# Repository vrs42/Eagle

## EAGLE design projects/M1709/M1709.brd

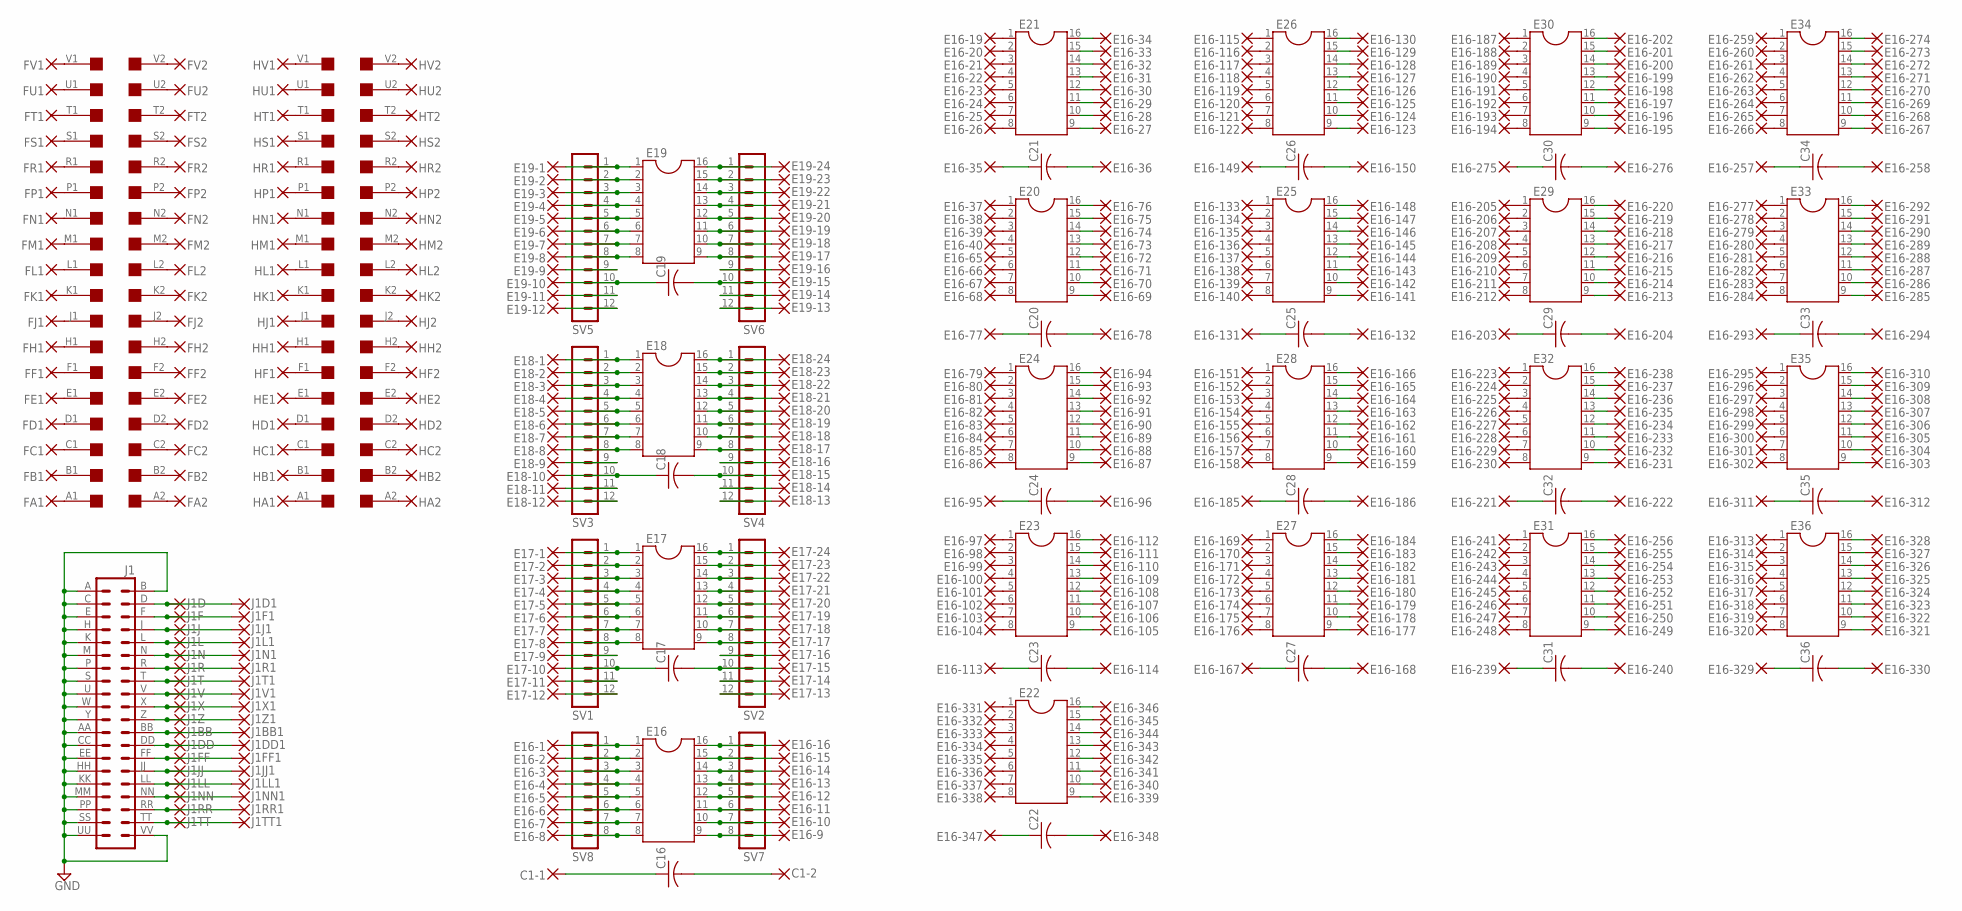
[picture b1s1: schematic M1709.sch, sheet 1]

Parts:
C1-1, C1-2: 1,6/0,8
C16, C17, C18, C19, C20, C21, C22, C23, C24, C25, C26, C27, C28, C29, C30, C31, C32, C33, C34, C35, C36: C-US075-032X103; C075-032X103
E16, E17, E18, E19, E20, E21, E22, E23, E24, E25, E26, E27, E28, E29, E30, E31, E32, E33, E34, E35, E36: DIL16
E16-1, E16-2, E16-3, E16-4, E16-5, E16-6, E16-7, E16-8, E16-9, E16-10, E16-11, E16-12, E16-13, E16-14, E16-15, E16-16, E17-1, E17-2, E17-3, E17-4, E17-5, E17-6, E17-7, E17-8, E17-9, E17-10, E17-11, E17-12, E17-13, E17-14, E17-15, E17-16, E17-17, E17-18, E17-19, E17-20, E17-21, E17-22, E17-23, E17-24, E18-1, E18-2, E18-3, E18-4, E18-5, E18-6, E18-7, E18-8, E18-9, E18-10, E18-11, E18-12, E18-13, E18-14, E18-15, E18-16, E18-17, E18-18, E18-19, E18-20, E18-21, E18-22, E18-23, E18-24, E19-1, E19-2, E19-3, E19-4, E19-5, E19-6, E19-7, E19-8, E19-9, E19-10, E19-11, E19-12, E19-13, E19-14, E19-15, E19-16, E19-17, E19-18, E19-19, E19-20, E19-21, E19-22, E19-23, E19-24: 1,6/0,8
E16-19, E16-20, E16-21, E16-22, E16-23, E16-24, E16-25, E16-26, E16-27, E16-28, E16-29, E16-30, E16-31, E16-32, E16-33, E16-34, E16-35, E16-36, E16-37, E16-38, E16-39, E16-40, E16-65, E16-66, E16-67, E16-68, E16-69, E16-70, E16-71, E16-72, E16-73, E16-74, E16-75, E16-76, E16-77, E16-78, E16-79, E16-80, E16-81, E16-82, E16-83, E16-84, E16-85, E16-86, E16-87, E16-88, E16-89, E16-90, E16-91, E16-92, E16-93, E16-94, E16-95, E16-96, E16-97, E16-98, E16-99, E16-100, E16-101, E16-102, E16-103, E16-104, E16-105, E16-106, E16-107, E16-108, E16-109, E16-110, E16-111, E16-112, E16-113, E16-114, E16-115, E16-116, E16-117, E16-118, E16-119, E16-120, E16-121, E16-122, E16-123, E16-124, E16-125, E16-126, E16-127, E16-128, E16-129, E16-130, E16-131, E16-132, E16-133, E16-134, E16-135, E16-136, E16-137, E16-138, E16-139, E16-140, E16-141, E16-142, E16-143, E16-144, E16-145, E16-146, E16-147, E16-148, E16-149, E16-150, E16-151, E16-152, E16-153, E16-154, E16-155, E16-156, E16-157, E16-158, E16-159, E16-160, E16-161, E16-162, E16-163, E16-164, E16-165, E16-166, E16-167, E16-168, E16-169, E16-170, E16-171, E16-172, E16-173, E16-174, E16-175, E16-176, E16-177, E16-178, E16-179, E16-180, E16-181, E16-182, E16-183, E16-184, E16-185, E16-186, E16-187, E16-188, E16-189, E16-190, E16-191, E16-192, E16-193, E16-194, E16-195, E16-196, E16-197, E16-198, E16-199, E16-200, E16-201, E16-202, E16-203, E16-204, E16-205, E16-206, E16-207, E16-208, E16-209, E16-210, E16-211, E16-212, E16-213, E16-214, E16-215, E16-216, E16-217, E16-218, E16-219, E16-220, E16-221, E16-222, E16-223, E16-224, E16-225, E16-226, E16-227, E16-228, E16-229, E16-230, E16-231, E16-232, E16-233, E16-234, E16-235, E16-236, E16-237, E16-238, E16-239, E16-240, E16-241, E16-242, E16-243, E16-244, E16-245, E16-246, E16-247, E16-248, E16-249, E16-250, E16-251, E16-252, E16-253, E16-254, E16-255, E16-256, E16-257, E16-258, E16-259, E16-260, E16-261, E16-262, E16-263, E16-264, E16-265, E16-266, E16-267, E16-268, E16-269, E16-270, E16-271, E16-272, E16-273, E16-274, E16-275, E16-276, E16-277, E16-278, E16-279, E16-280, E16-281, E16-282, E16-283, E16-284, E16-285, E16-286, E16-287, E16-288, E16-289, E16-290, E16-291, E16-292, E16-293, E16-294, E16-295, E16-296, E16-297, E16-298, E16-299, E16-300, E16-301, E16-302, E16-303, E16-304, E16-305, E16-306, E16-307, E16-308, E16-309, E16-310, E16-311, E16-312, E16-313, E16-314, E16-315, E16-316, E16-317, E16-318, E16-319, E16-320, E16-321, E16-322, E16-323, E16-324, E16-325, E16-326, E16-327, E16-328, E16-329, E16-330, E16-331, E16-332, E16-333, E16-334, E16-335, E16-336, E16-337, E16-338, E16-339, E16-340, E16-341, E16-342, E16-343, E16-344, E16-345, E16-346, E16-347, E16-348: 2,54/0,8
F: SINGLE; EDGE-CON2
FA1, FA2: 2,54/0,8
FB1, FB2: 2,54/0,8
FC1, FC2: 2,54/0,8
FD1, FD2: 2,54/0,8
FE1, FE2: 2,54/0,8
FF1, FF2: 2,54/0,8
FH1, FH2: 2,54/0,8
FJ1, FJ2: 2,54/0,8
FK1, FK2: 2,54/0,8
FL1, FL2: 2,54/0,8
FM1, FM2: 2,54/0,8
FN1, FN2: 2,54/0,8
FP1, FP2: 2,54/0,8
FR1, FR2: 2,54/0,8
FS1, FS2: 2,54/0,8
FT1, FT2: 2,54/0,8
FU1, FU2: 2,54/0,8
FV1, FV2: 2,54/0,8
H: SINGLE; EDGE-CON2
HA1, HA2: 2,54/0,8
HB1, HB2: 2,54/0,8
HC1, HC2: 2,54/0,8
HD1, HD2: 2,54/0,8
HE1, HE2: 2,54/0,8
HF1, HF2: 2,54/0,8
HH1, HH2: 2,54/0,8
HJ1, HJ2: 2,54/0,8
HK1, HK2: 2,54/0,8
HL1, HL2: 2,54/0,8
HM1, HM2: 2,54/0,8
HN1, HN2: 2,54/0,8
HP1, HP2: 2,54/0,8
HR1, HR2: 2,54/0,8
HS1, HS2: 2,54/0,8
HT1, HT2: 2,54/0,8
HU1, HU2: 2,54/0,8
HV1, HV2: 2,54/0,8
J1: DEC40PINH
J1BB, J1BB1, J1D, J1D1, J1DD, J1DD1, J1F, J1F1, J1FF, J1FF1, J1J, J1J1, J1JJ, J1JJ1, J1L, J1L1, J1LL, J1LL1, J1N, J1N1, J1NN, J1NN1, J1R, J1R1, J1RR, J1RR1, J1T, J1T1, J1TT, J1TT1, J1V, J1V1, J1X, J1X1, J1Z, J1Z1: 2,54/0,8
SV1, SV2, SV3, SV4, SV5, SV6: MA12-1
SV7, SV8: MA08-1

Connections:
GND: J1.A (1), J1.AA (23), J1.B (2), J1.C (3), J1.CC (25), J1.E (5), J1.EE (27), J1.H (7), J1.HH (29), J1.K (9), J1.KK (31), J1.M (11), J1.MM (33), J1.P (13), J1.PP (35), J1.S (15), J1.SS (37), J1.U (17), J1.UU (39), J1.VV (40), J1.W (19), J1.Y (21); also elsewhere on the board
unnamed: J1.D (4), J1D.1, J1D1.1
unnamed: J1.F (6), J1F.1, J1F1.1
unnamed: J1.J (8), J1J.1, J1J1.1
unnamed: J1.L (10), J1L.1, J1L1.1
unnamed: J1.N (12), J1N.1, J1N1.1
unnamed: J1.R (14), J1R.1, J1R1.1
unnamed: J1.T (16), J1T.1, J1T1.1
unnamed: J1.V (18), J1V.1, J1V1.1
unnamed: J1.X (20), J1X.1, J1X1.1
unnamed: J1.Z (22), J1Z.1, J1Z1.1
unnamed: J1.BB (24), J1BB.1, J1BB1.1
unnamed: J1.DD (26), J1DD.1, J1DD1.1
unnamed: J1.FF (28), J1FF.1, J1FF1.1
unnamed: J1.JJ (30), J1JJ.1, J1JJ1.1
unnamed: J1.LL (32), J1LL.1, J1LL1.1
unnamed: J1.NN (34), J1NN.1, J1NN1.1
unnamed: J1.RR (36), J1RR.1, J1RR1.1
unnamed: J1.TT (38), J1TT.1, J1TT1.1
unnamed: F.A1, FA1.1
unnamed: F.B1, FB1.1
unnamed: F.C1, FC1.1
unnamed: F.D1, FD1.1
unnamed: F.E1, FE1.1
unnamed: F.F1, FF1.1
unnamed: F.H1, FH1.1
unnamed: F.J1, FJ1.1
unnamed: F.K1, FK1.1
unnamed: F.L1, FL1.1
unnamed: F.M1, FM1.1
unnamed: F.N1, FN1.1
unnamed: F.P1, FP1.1
unnamed: F.R1, FR1.1
unnamed: F.S1, FS1.1
unnamed: F.T1, FT1.1
unnamed: F.U1, FU1.1
unnamed: F.V1, FV1.1
unnamed: F.A2, FA2.1
unnamed: F.B2, FB2.1
unnamed: F.C2, FC2.1
unnamed: F.D2, FD2.1
unnamed: F.E2, FE2.1
unnamed: F.F2, FF2.1
unnamed: F.H2, FH2.1
unnamed: F.J2, FJ2.1
unnamed: F.K2, FK2.1
unnamed: F.L2, FL2.1
unnamed: F.M2, FM2.1
unnamed: F.N2, FN2.1
unnamed: F.P2, FP2.1
unnamed: F.R2, FR2.1
unnamed: F.S2, FS2.1
unnamed: F.T2, FT2.1
unnamed: F.U2, FU2.1
unnamed: F.V2, FV2.1
unnamed: H.A2, HA2.1
unnamed: H.B2, HB2.1
unnamed: H.C2, HC2.1
unnamed: H.D2, HD2.1
unnamed: H.E2, HE2.1
unnamed: H.F2, HF2.1
unnamed: H.H2, HH2.1
unnamed: H.J2, HJ2.1
unnamed: H.K2, HK2.1
unnamed: H.L2, HL2.1
unnamed: H.M2, HM2.1
unnamed: H.N2, HN2.1
unnamed: H.P2, HP2.1
unnamed: H.R2, HR2.1
unnamed: H.S2, HS2.1
unnamed: H.T2, HT2.1
unnamed: H.U2, HU2.1
unnamed: H.V2, HV2.1
unnamed: H.A1, HA1.1
unnamed: H.B1, HB1.1
unnamed: H.C1, HC1.1
unnamed: H.D1, HD1.1
unnamed: H.E1, HE1.1
unnamed: H.F1, HF1.1
unnamed: H.H1, HH1.1
unnamed: H.J1, HJ1.1
unnamed: H.K1, HK1.1
unnamed: H.L1, HL1.1
unnamed: H.M1, HM1.1
unnamed: H.N1, HN1.1
unnamed: H.P1, HP1.1
unnamed: H.R1, HR1.1
unnamed: H.S1, HS1.1
unnamed: H.T1, HT1.1
unnamed: H.U1, HU1.1
unnamed: H.V1, HV1.1
unnamed: E17.1, E17-1.1, SV1.1
unnamed: E17.2, E17-2.1, SV1.2
unnamed: E17.3, E17-3.1, SV1.3
unnamed: E17.4, E17-4.1, SV1.4
unnamed: E17.5, E17-5.1, SV1.5
unnamed: E17.6, E17-6.1, SV1.6
unnamed: E17.7, E17-7.1, SV1.7
unnamed: E17.8, E17-8.1, SV1.8
unnamed: E17-9.1, SV1.9
unnamed: C17.1, E17-10.1, SV1.10
unnamed: C17.2, E17-15.1, SV2.10
unnamed: E17-16.1, SV2.9
unnamed: E17.9, E17-17.1, SV2.8
unnamed: E17.10, E17-18.1, SV2.7
unnamed: E17.11, E17-19.1, SV2.6
unnamed: E17.12, E17-20.1, SV2.5
unnamed: E17.13, E17-21.1, SV2.4
unnamed: E17.14, E17-22.1, SV2.3
unnamed: E17.15, E17-23.1, SV2.2
unnamed: E17.16, E17-24.1, SV2.1
unnamed: E18-11.1, SV3.11
unnamed: E18-12.1, SV3.12
unnamed: E18-13.1, SV4.12
unnamed: E18-14.1, SV4.11
unnamed: E18.1, E18-1.1, SV3.1
unnamed: E18.2, E18-2.1, SV3.2
unnamed: E17-11.1, SV1.11
unnamed: E17-12.1, SV1.12
unnamed: E16.1, E16-1.1, SV8.1
unnamed: E16.2, E16-2.1, SV8.2
unnamed: E16.3, E16-3.1, SV8.3
unnamed: E16.4, E16-4.1, SV8.4
unnamed: E16.5, E16-5.1, SV8.5
unnamed: E16.6, E16-6.1, SV8.6
unnamed: E16.7, E16-7.1, SV8.7
unnamed: E16.8, E16-8.1, SV8.8
unnamed: E16.9, E16-9.1, SV7.8
unnamed: E16.10, E16-10.1, SV7.7
unnamed: E16.11, E16-11.1, SV7.6
unnamed: E16.12, E16-12.1, SV7.5
unnamed: E16.13, E16-13.1, SV7.4
unnamed: E16.14, E16-14.1, SV7.3
unnamed: E16.15, E16-15.1, SV7.2
unnamed: E16.16, E16-16.1, SV7.1
unnamed: E17-13.1, SV2.12
unnamed: E17-14.1, SV2.11
unnamed: E18.3, E18-3.1, SV3.3
unnamed: E18.4, E18-4.1, SV3.4
unnamed: E18.5, E18-5.1, SV3.5
unnamed: E18.6, E18-6.1, SV3.6
unnamed: E18.7, E18-7.1, SV3.7
unnamed: E18.8, E18-8.1, SV3.8
unnamed: E18-9.1, SV3.9
unnamed: C18.1, E18-10.1, SV3.10
unnamed: C18.2, E18-15.1, SV4.10
unnamed: E18-16.1, SV4.9
unnamed: E18.9, E18-17.1, SV4.8
unnamed: E18.10, E18-18.1, SV4.7
unnamed: E18.11, E18-19.1, SV4.6
unnamed: E18.12, E18-20.1, SV4.5
unnamed: E18.13, E18-21.1, SV4.4
unnamed: E18.14, E18-22.1, SV4.3
unnamed: E18.15, E18-23.1, SV4.2
unnamed: E18.16, E18-24.1, SV4.1
unnamed: E19-11.1, SV5.11
unnamed: E19-12.1, SV5.12
unnamed: E19-13.1, SV6.12
unnamed: E19-14.1, SV6.11
unnamed: E19.1, E19-1.1, SV5.1
unnamed: E19.2, E19-2.1, SV5.2
unnamed: E19.3, E19-3.1, SV5.3
unnamed: E19.4, E19-4.1, SV5.4
unnamed: E19.5, E19-5.1, SV5.5
unnamed: E19.6, E19-6.1, SV5.6
unnamed: E19.7, E19-7.1, SV5.7
unnamed: E19.8, E19-8.1, SV5.8
unnamed: E19-9.1, SV5.9
unnamed: C19.1, E19-10.1, SV5.10
unnamed: C19.2, E19-15.1, SV6.10
unnamed: E19-16.1, SV6.9
unnamed: E19.9, E19-17.1, SV6.8
unnamed: E19.10, E19-18.1, SV6.7
unnamed: E19.11, E19-19.1, SV6.6
unnamed: E19.12, E19-20.1, SV6.5
unnamed: E19.13, E19-21.1, SV6.4
unnamed: E19.14, E19-22.1, SV6.3
unnamed: E19.15, E19-23.1, SV6.2
unnamed: E19.16, E19-24.1, SV6.1
unnamed: C1-1.1, C16.1
unnamed: C1-2.1, C16.2
unnamed: E16-19.1, E21.1
unnamed: E16-20.1, E21.2
unnamed: E16-21.1, E21.3
unnamed: E16-22.1, E21.4
unnamed: E16-23.1, E21.5
unnamed: E16-24.1, E21.6
unnamed: E16-25.1, E21.7
unnamed: E16-26.1, E21.8
unnamed: E16-27.1, E21.9
unnamed: E16-28.1, E21.10
unnamed: E16-29.1, E21.11
unnamed: E16-30.1, E21.12
unnamed: E16-31.1, E21.13
unnamed: E16-32.1, E21.14
unnamed: E16-33.1, E21.15
unnamed: E16-34.1, E21.16
unnamed: C21.1, E16-35.1
unnamed: C21.2, E16-36.1
unnamed: E16-37.1, E20.1
unnamed: E16-38.1, E20.2
unnamed: E16-39.1, E20.3
unnamed: E16-40.1, E20.4
unnamed: E16-65.1, E20.5
unnamed: E16-66.1, E20.6
unnamed: E16-67.1, E20.7
unnamed: E16-68.1, E20.8
unnamed: E16-69.1, E20.9
unnamed: E16-70.1, E20.10
unnamed: E16-71.1, E20.11
unnamed: E16-72.1, E20.12
unnamed: E16-73.1, E20.13
unnamed: E16-74.1, E20.14
unnamed: E16-75.1, E20.15
unnamed: E16-76.1, E20.16
unnamed: C20.1, E16-77.1
unnamed: C20.2, E16-78.1
unnamed: E16-79.1, E24.1
unnamed: E16-80.1, E24.2
unnamed: E16-81.1, E24.3
unnamed: E16-82.1, E24.4
unnamed: E16-83.1, E24.5
unnamed: E16-84.1, E24.6
unnamed: E16-85.1, E24.7
unnamed: E16-86.1, E24.8
unnamed: E16-87.1, E24.9
unnamed: E16-88.1, E24.10
unnamed: E16-89.1, E24.11
unnamed: E16-90.1, E24.12
unnamed: E16-91.1, E24.13
unnamed: E16-92.1, E24.14
unnamed: E16-93.1, E24.15
unnamed: E16-94.1, E24.16
unnamed: C24.1, E16-95.1
unnamed: C24.2, E16-96.1
unnamed: E16-97.1, E23.1
unnamed: E16-98.1, E23.2
unnamed: E16-99.1, E23.3
unnamed: E16-100.1, E23.4
unnamed: E16-101.1, E23.5
unnamed: E16-102.1, E23.6
unnamed: E16-103.1, E23.7
unnamed: E16-104.1, E23.8
unnamed: E16-105.1, E23.9
unnamed: E16-106.1, E23.10
unnamed: E16-107.1, E23.11
unnamed: E16-108.1, E23.12
unnamed: E16-109.1, E23.13
unnamed: E16-110.1, E23.14
unnamed: E16-111.1, E23.15
unnamed: E16-112.1, E23.16
unnamed: C23.1, E16-113.1
unnamed: C23.2, E16-114.1
unnamed: E16-115.1, E26.1
unnamed: E16-116.1, E26.2
unnamed: E16-117.1, E26.3
unnamed: E16-118.1, E26.4
unnamed: E16-119.1, E26.5
unnamed: E16-120.1, E26.6
unnamed: E16-121.1, E26.7
unnamed: E16-122.1, E26.8
unnamed: E16-123.1, E26.9
unnamed: E16-124.1, E26.10
unnamed: E16-125.1, E26.11
unnamed: E16-126.1, E26.12
unnamed: E16-127.1, E26.13
unnamed: E16-128.1, E26.14
unnamed: E16-129.1, E26.15
unnamed: E16-130.1, E26.16
unnamed: C25.1, E16-131.1
unnamed: C25.2, E16-132.1
unnamed: E16-133.1, E25.1
unnamed: E16-134.1, E25.2
unnamed: E16-135.1, E25.3
unnamed: E16-136.1, E25.4
unnamed: E16-137.1, E25.5
unnamed: E16-138.1, E25.6
unnamed: E16-139.1, E25.7
unnamed: E16-140.1, E25.8
unnamed: E16-141.1, E25.9
unnamed: E16-142.1, E25.10
unnamed: E16-143.1, E25.11
unnamed: E16-144.1, E25.12
unnamed: E16-145.1, E25.13
unnamed: E16-146.1, E25.14
unnamed: E16-147.1, E25.15
unnamed: E16-148.1, E25.16
unnamed: C26.1, E16-149.1
unnamed: C26.2, E16-150.1
unnamed: E16-151.1, E28.1
unnamed: E16-152.1, E28.2
unnamed: E16-153.1, E28.3
unnamed: E16-154.1, E28.4
unnamed: E16-155.1, E28.5
unnamed: E16-156.1, E28.6
unnamed: E16-157.1, E28.7
unnamed: E16-158.1, E28.8
unnamed: E16-159.1, E28.9
unnamed: E16-160.1, E28.10
unnamed: E16-161.1, E28.11
unnamed: E16-162.1, E28.12
unnamed: E16-163.1, E28.13
unnamed: E16-164.1, E28.14
unnamed: E16-165.1, E28.15
unnamed: E16-166.1, E28.16
unnamed: C27.1, E16-167.1
unnamed: C27.2, E16-168.1
unnamed: E16-169.1, E27.1
unnamed: E16-170.1, E27.2
unnamed: E16-171.1, E27.3
unnamed: E16-172.1, E27.4
unnamed: E16-173.1, E27.5
unnamed: E16-174.1, E27.6
unnamed: E16-175.1, E27.7
unnamed: E16-176.1, E27.8
unnamed: E16-177.1, E27.9
unnamed: E16-178.1, E27.10
unnamed: E16-179.1, E27.11
unnamed: E16-180.1, E27.12
unnamed: E16-181.1, E27.13
unnamed: E16-182.1, E27.14
unnamed: E16-183.1, E27.15
unnamed: E16-184.1, E27.16
unnamed: C28.1, E16-185.1
unnamed: C28.2, E16-186.1
unnamed: E16-187.1, E30.1
unnamed: E16-188.1, E30.2
unnamed: E16-189.1, E30.3
unnamed: E16-190.1, E30.4
unnamed: E16-191.1, E30.5
unnamed: E16-192.1, E30.6
unnamed: E16-193.1, E30.7
unnamed: E16-194.1, E30.8
unnamed: E16-195.1, E30.9
unnamed: E16-196.1, E30.10
unnamed: E16-197.1, E30.11
unnamed: E16-198.1, E30.12
unnamed: E16-199.1, E30.13
unnamed: E16-200.1, E30.14
unnamed: E16-201.1, E30.15
unnamed: E16-202.1, E30.16
unnamed: C29.1, E16-203.1
unnamed: C29.2, E16-204.1
unnamed: E16-205.1, E29.1
unnamed: E16-206.1, E29.2
unnamed: E16-207.1, E29.3
unnamed: E16-208.1, E29.4
unnamed: E16-209.1, E29.5
unnamed: E16-210.1, E29.6
unnamed: E16-211.1, E29.7
unnamed: E16-212.1, E29.8
unnamed: E16-213.1, E29.9
unnamed: E16-214.1, E29.10
unnamed: E16-215.1, E29.11
unnamed: E16-216.1, E29.12
unnamed: E16-217.1, E29.13
unnamed: E16-218.1, E29.14
unnamed: E16-219.1, E29.15
unnamed: E16-220.1, E29.16
unnamed: C32.1, E16-221.1
unnamed: C32.2, E16-222.1
unnamed: E16-223.1, E32.1
unnamed: E16-224.1, E32.2
unnamed: E16-225.1, E32.3
unnamed: E16-226.1, E32.4
unnamed: E16-227.1, E32.5
unnamed: E16-228.1, E32.6
unnamed: E16-229.1, E32.7
unnamed: E16-230.1, E32.8
unnamed: E16-231.1, E32.9
unnamed: E16-232.1, E32.10
unnamed: E16-233.1, E32.11
unnamed: E16-234.1, E32.12
unnamed: E16-235.1, E32.13
unnamed: E16-236.1, E32.14
unnamed: E16-237.1, E32.15
unnamed: E16-238.1, E32.16
unnamed: C31.1, E16-239.1
unnamed: C31.2, E16-240.1
unnamed: E16-241.1, E31.1
unnamed: E16-242.1, E31.2
unnamed: E16-243.1, E31.3
unnamed: E16-244.1, E31.4
unnamed: E16-245.1, E31.5
unnamed: E16-246.1, E31.6
unnamed: E16-247.1, E31.7
unnamed: E16-248.1, E31.8
unnamed: E16-249.1, E31.9
unnamed: E16-250.1, E31.10
unnamed: E16-251.1, E31.11
unnamed: E16-252.1, E31.12
unnamed: E16-253.1, E31.13
unnamed: E16-254.1, E31.14
unnamed: E16-255.1, E31.15
unnamed: E16-256.1, E31.16
unnamed: C34.1, E16-257.1
unnamed: C34.2, E16-258.1
unnamed: E16-259.1, E34.1
unnamed: E16-260.1, E34.2
unnamed: E16-261.1, E34.3
unnamed: E16-262.1, E34.4
unnamed: E16-263.1, E34.5
unnamed: E16-264.1, E34.6
unnamed: E16-265.1, E34.7
unnamed: E16-266.1, E34.8
unnamed: E16-267.1, E34.9
unnamed: E16-268.1, E34.10
unnamed: E16-269.1, E34.11
unnamed: E16-270.1, E34.12
unnamed: E16-271.1, E34.13
unnamed: E16-272.1, E34.14
unnamed: E16-273.1, E34.15
unnamed: E16-274.1, E34.16
unnamed: C30.1, E16-275.1
unnamed: C30.2, E16-276.1
unnamed: E16-277.1, E33.1
unnamed: E16-278.1, E33.2
unnamed: E16-279.1, E33.3
unnamed: E16-280.1, E33.4
unnamed: E16-281.1, E33.5
unnamed: E16-282.1, E33.6
unnamed: E16-283.1, E33.7
unnamed: E16-284.1, E33.8
unnamed: E16-285.1, E33.9
unnamed: E16-286.1, E33.10
unnamed: E16-287.1, E33.11
unnamed: E16-288.1, E33.12
unnamed: E16-289.1, E33.13
unnamed: E16-290.1, E33.14
unnamed: E16-291.1, E33.15
unnamed: E16-292.1, E33.16
unnamed: C33.1, E16-293.1
unnamed: C33.2, E16-294.1
unnamed: E16-295.1, E35.1
unnamed: E16-296.1, E35.2
unnamed: E16-297.1, E35.3
unnamed: E16-298.1, E35.4
unnamed: E16-299.1, E35.5
unnamed: E16-300.1, E35.6
unnamed: E16-301.1, E35.7
unnamed: E16-302.1, E35.8
unnamed: E16-303.1, E35.9
unnamed: E16-304.1, E35.10
unnamed: E16-305.1, E35.11
unnamed: E16-306.1, E35.12
unnamed: E16-307.1, E35.13
unnamed: E16-308.1, E35.14
unnamed: E16-309.1, E35.15
unnamed: E16-310.1, E35.16
unnamed: C35.1, E16-311.1
unnamed: C35.2, E16-312.1
unnamed: E16-313.1, E36.1
unnamed: E16-314.1, E36.2
unnamed: E16-315.1, E36.3
unnamed: E16-316.1, E36.4
unnamed: E16-317.1, E36.5
unnamed: E16-318.1, E36.6
unnamed: E16-319.1, E36.7
unnamed: E16-320.1, E36.8
unnamed: E16-321.1, E36.9
unnamed: E16-322.1, E36.10
unnamed: E16-323.1, E36.11
unnamed: E16-324.1, E36.12
unnamed: E16-325.1, E36.13
unnamed: E16-326.1, E36.14
unnamed: E16-327.1, E36.15
unnamed: E16-328.1, E36.16
unnamed: C36.1, E16-329.1
unnamed: C36.2, E16-330.1
unnamed: E16-331.1, E22.1
unnamed: E16-332.1, E22.2
unnamed: E16-333.1, E22.3
unnamed: E16-334.1, E22.4
unnamed: E16-335.1, E22.5
unnamed: E16-336.1, E22.6
unnamed: E16-337.1, E22.7
unnamed: E16-338.1, E22.8
unnamed: E16-339.1, E22.9
unnamed: E16-340.1, E22.10
unnamed: E16-341.1, E22.11
unnamed: E16-342.1, E22.12
unnamed: E16-343.1, E22.13
unnamed: E16-344.1, E22.14
unnamed: E16-345.1, E22.15
unnamed: E16-346.1, E22.16
unnamed: C22.1, E16-347.1
unnamed: C22.2, E16-348.1

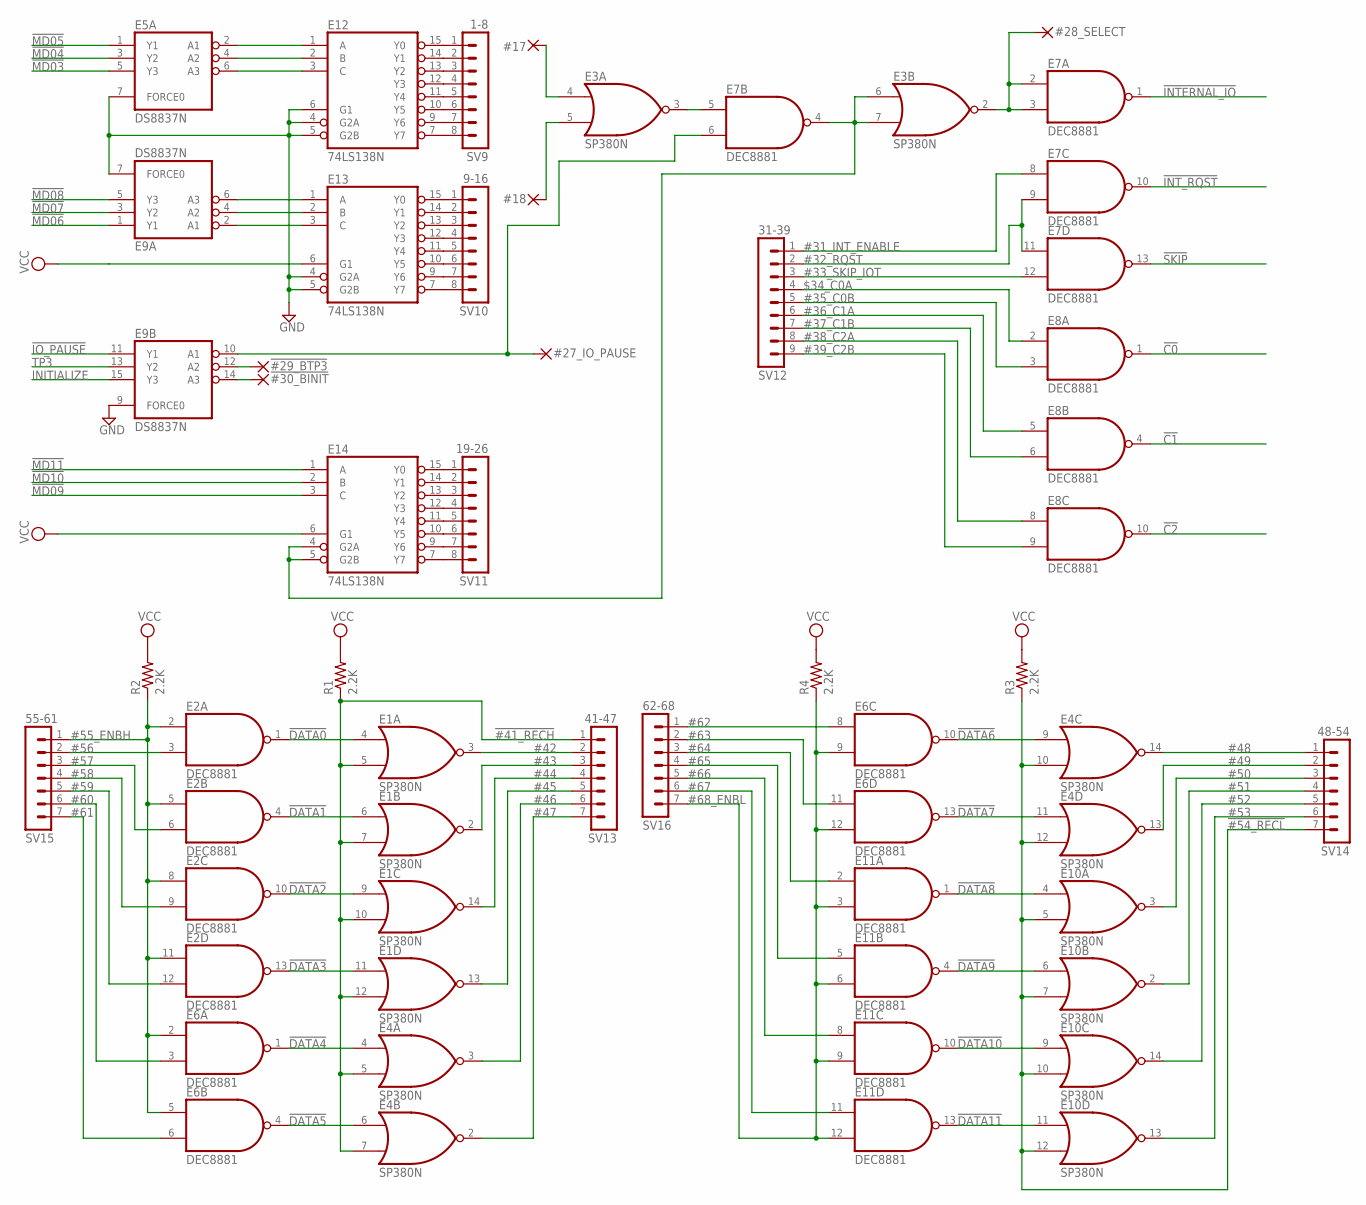
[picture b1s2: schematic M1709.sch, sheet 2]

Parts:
!#29_BTP3: 29; 2,54/0,8
!#30_BINIT: 30; 2,54/0,8
#17: 17; 2,54/0,8
#18: 18; 2,54/0,8
#27_IO_PAUSE: 27; 2,54/0,8
#28_SELECT: 28; 2,54/0,8
E1, E3, E4, E10: SP380N; DIL14
E2, E6, E7, E8, E11: DEC8881; DIL14
E5, E9: DS8837N; DIL16
E12, E13, E14: 74LS138N; DIL16
R1, R2, R3, R4: 2.2K; 0207/10
SV9: 1-8; MA08-1
SV10: 9-16; MA08-1
SV11: 19-26; MA08-1
SV12: 31-39; MA09-1
SV13: 41-47; MA07-1
SV14: 48-54; MA07-1
SV15: 55-61; MA07-1
SV16: 62-68; MA07-1

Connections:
!#41_RECH: E1.5 (I1), E1.7 (I1), E1.10 (I1), E1.12 (I1), E4.5 (I1), E4.7 (I1), R1.1, SV13.1
!#54_RECL: E4.10 (I1), E4.12 (I1), E10.5 (I1), E10.7 (I1), E10.10 (I1), E10.12 (I1), R3.1, SV14.7
!C0: E8.1 (O); also elsewhere on the board
!C1: E8.4 (O); also elsewhere on the board
!C2: E8.10 (O); also elsewhere on the board
!DATA0: E1.4 (I0), E2.1 (O); also elsewhere on the board
!DATA1: E1.6 (I0), E2.4 (O); also elsewhere on the board
!DATA2: E1.9 (I0), E2.10 (O); also elsewhere on the board
!DATA3: E1.11 (I0), E2.13 (O); also elsewhere on the board
!DATA4: E4.4 (I0), E6.1 (O); also elsewhere on the board
!DATA5: E4.6 (I0), E6.4 (O); also elsewhere on the board
!DATA6: E4.9 (I0), E6.10 (O); also elsewhere on the board
!DATA7: E4.11 (I0), E6.13 (O); also elsewhere on the board
!DATA8: E10.4 (I0), E11.1 (O); also elsewhere on the board
!DATA9: E10.6 (I0), E11.4 (O); also elsewhere on the board
!DATA10: E10.9 (I0), E11.10 (O); also elsewhere on the board
!DATA11: E10.11 (I0), E11.13 (O); also elsewhere on the board
!INTERNAL_IO: E7.1 (O); also elsewhere on the board
!INT_RQST: E7.10 (O); also elsewhere on the board
!IO_PAUSE: E9.11 (Y1); also elsewhere on the board
!MD03: E5.5 (Y3); also elsewhere on the board
!MD04: E5.3 (Y2); also elsewhere on the board
!MD05: E5.1 (Y1); also elsewhere on the board
!MD06: E9.1 (Y1); also elsewhere on the board
!MD07: E9.3 (Y2); also elsewhere on the board
!MD08: E9.5 (Y3); also elsewhere on the board
!MD09: E14.3 (C); also elsewhere on the board
!MD10: E14.2 (B); also elsewhere on the board
!MD11: E14.1 (A); also elsewhere on the board
!SKIP: E7.13 (O); also elsewhere on the board
#31_INT_ENABLE: E7.8 (I0), SV12.1
#32_RQST: E7.9 (I1), E7.11 (I0), SV12.2
#33_SKIP_IOT: E7.12 (I1), SV12.3
#35_C0B: E8.3 (I1), SV12.5
#36_C1A: E8.5 (I0), SV12.6
#37_C1B: E8.6 (I1), SV12.7
#38_C2A: E8.8 (I0), SV12.8
#39_C2B: E8.9 (I1), SV12.9
#42: E1.3 (O), SV13.2
#43: E1.2 (O), SV13.3
#44: E1.14 (O), SV13.4
#45: E1.13 (O), SV13.5
#46: E4.3 (O), SV13.6
#47: E4.2 (O), SV13.7
#48: E4.14 (O), SV14.1
#49: E4.13 (O), SV14.2
#50: E10.3 (O), SV14.3
#51: E10.2 (O), SV14.4
#52: E10.14 (O), SV14.5
#53: E10.13 (O), SV14.6
#55_ENBH: E2.2 (I0), E2.5 (I0), E2.8 (I0), E2.11 (I0), E6.2 (I0), E6.5 (I0), R2.1, SV15.1
#56: E2.3 (I1), SV15.2
#57: E2.6 (I1), SV15.3
#58: E2.9 (I1), SV15.4
#59: E2.12 (I1), SV15.5
#60: E6.3 (I1), SV15.6
#61: E6.6 (I1), SV15.7
#62: E6.8 (I0), SV16.1
#63: E6.11 (I0), SV16.2
#64: E11.2 (I0), SV16.3
#65: E11.5 (I0), SV16.4
#66: E11.8 (I0), SV16.5
#67: E11.11 (I0), SV16.6
#68_ENBL: E6.9 (I1), E6.12 (I1), E11.3 (I1), E11.6 (I1), E11.9 (I1), E11.12 (I1), R4.1, SV16.7
$34_C0A: E8.2 (I0), SV12.4
GND: E1.1 (GND), E2.7 (GND), E3.1 (GND), E4.1 (GND), E5.7 (FORCE0), E5.8 (GND), E6.7 (GND), E7.7 (GND), E8.7 (GND), E9.7 (FORCE0), E9.8 (GND), E9.9 (FORCE0), E10.1 (GND), E11.7 (GND), E12.4 (G2A), E12.5 (G2B), E12.6 (G1), E12.8 (GND), E13.4 (G2A), E13.5 (G2B), E13.8 (GND), E14.8 (GND); also elsewhere on the board
INITIALIZE: E9.15 (Y3); also elsewhere on the board
unnamed: E12.15 (Y0), SV9.1
unnamed: E12.14 (Y1), SV9.2
unnamed: E12.13 (Y2), SV9.3
unnamed: E12.12 (Y3), SV9.4
unnamed: E12.11 (Y4), SV9.5
unnamed: E12.10 (Y5), SV9.6
unnamed: E12.9 (Y6), SV9.7
unnamed: E12.7 (Y7), SV9.8
unnamed: E13.15 (Y0), SV10.1
unnamed: E13.14 (Y1), SV10.2
unnamed: E13.13 (Y2), SV10.3
unnamed: E13.12 (Y3), SV10.4
unnamed: E13.11 (Y4), SV10.5
unnamed: E13.10 (Y5), SV10.6
unnamed: E13.9 (Y6), SV10.7
unnamed: E13.7 (Y7), SV10.8
unnamed: E5.2 (A1), E12.1 (A)
unnamed: E5.4 (A2), E12.2 (B)
unnamed: E5.6 (A3), E12.3 (C)
unnamed: E9.2 (A1), E13.3 (C)
unnamed: E9.4 (A2), E13.2 (B)
unnamed: E9.6 (A3), E13.1 (A)
unnamed: E3.6 (I0), E3.7 (I1), E7.4 (O), E14.4 (G2A), E14.5 (G2B)
unnamed: #17.1, E3.4 (I0)
unnamed: #18.1, E3.5 (I1)
unnamed: E3.3 (O), E7.5 (I0)
unnamed: E14.15 (Y0), SV11.1
unnamed: E14.14 (Y1), SV11.2
unnamed: E14.13 (Y2), SV11.3
unnamed: E14.12 (Y3), SV11.4
unnamed: E14.11 (Y4), SV11.5
unnamed: E14.10 (Y5), SV11.6
unnamed: E14.9 (Y6), SV11.7
unnamed: E14.7 (Y7), SV11.8
unnamed: #27_IO_PAUSE.1, E7.6 (I1), E9.10 (A1)
unnamed: #28_SELECT.1, E3.2 (O), E7.2 (I0), E7.3 (I1)
unnamed: !#30_BINIT.1, E9.14 (A3)
unnamed: !#29_BTP3.1, E9.12 (A2)
TP3: E9.13 (Y2); also elsewhere on the board
VCC: E1.8 (VCC), E2.14 (VCC), E3.8 (VCC), E4.8 (VCC), E5.16 (VCC), E6.14 (VCC), E7.14 (VCC), E8.14 (VCC), E9.16 (VCC), E10.8 (VCC), E11.14 (VCC), E12.16 (VCC), E13.6 (G1), E13.16 (VCC), E14.6 (G1), E14.16 (VCC), R1.2, R2.2, R3.2, R4.2; also elsewhere on the board

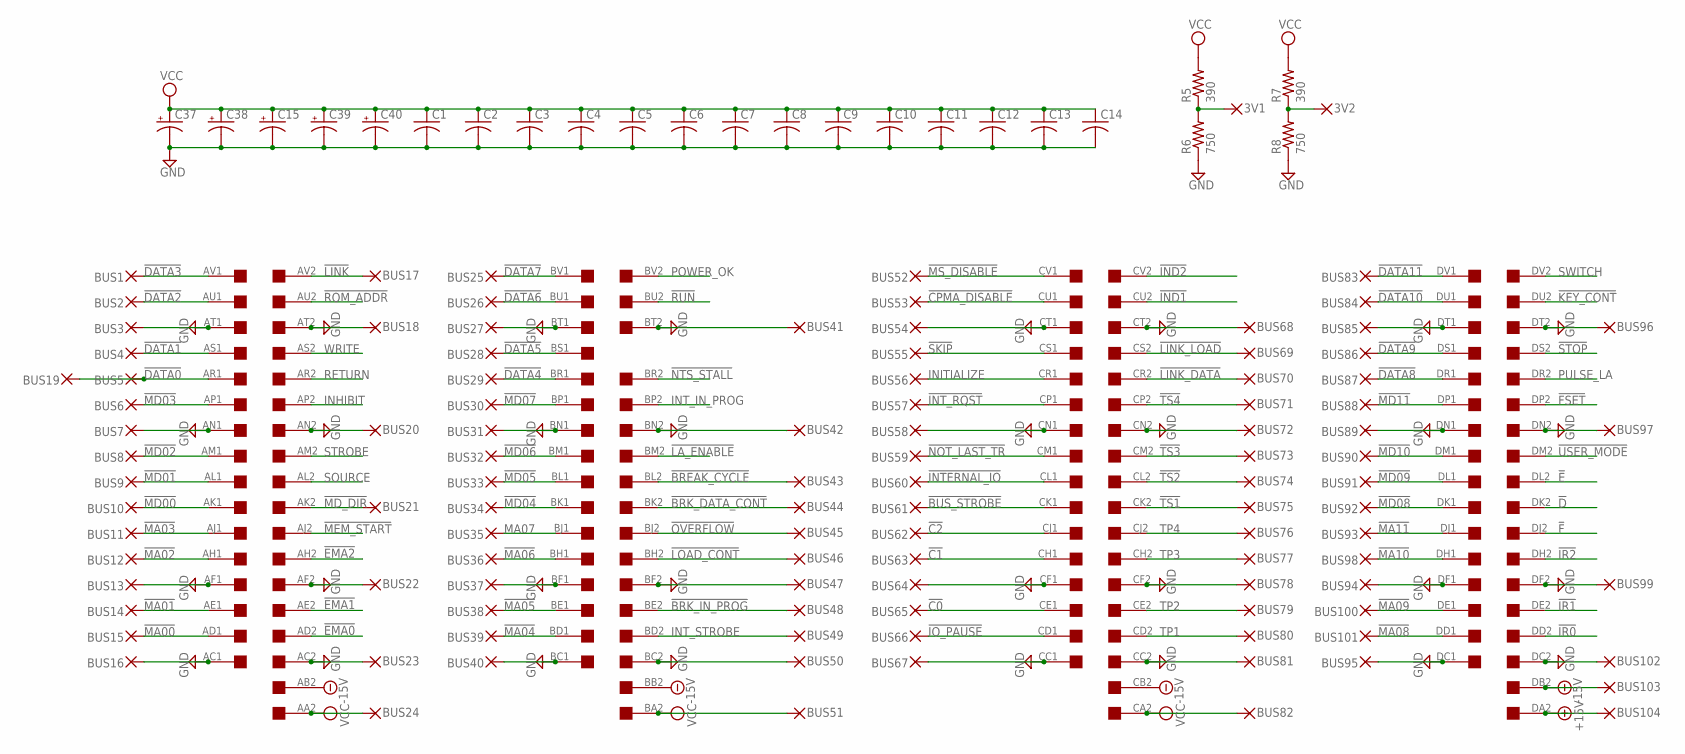
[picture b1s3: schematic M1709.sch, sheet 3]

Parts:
3V1, 3V2: 2,54/0,8
BUS1, BUS2, BUS3, BUS4, BUS5, BUS6, BUS7, BUS8, BUS9, BUS10, BUS11, BUS12, BUS13, BUS14, BUS15, BUS16, BUS17, BUS18, BUS19, BUS20, BUS21, BUS22, BUS23, BUS24, BUS25, BUS26, BUS27, BUS28, BUS29, BUS30, BUS31, BUS32, BUS33, BUS34, BUS35, BUS36, BUS37, BUS38, BUS39, BUS40, BUS41, BUS42, BUS43, BUS44, BUS45, BUS46, BUS47, BUS48, BUS49, BUS50, BUS51, BUS52, BUS53, BUS54, BUS55, BUS56, BUS57, BUS58, BUS59, BUS60, BUS61, BUS62, BUS63, BUS64, BUS65, BUS66, BUS67, BUS68, BUS69, BUS70, BUS71, BUS72, BUS73, BUS74, BUS75, BUS76, BUS77, BUS78, BUS79, BUS80, BUS81, BUS82, BUS83, BUS84, BUS85, BUS86, BUS87, BUS88, BUS89, BUS90, BUS91, BUS92, BUS93, BUS94, BUS95, BUS96, BUS97, BUS98, BUS99, BUS100, BUS101, BUS102, BUS103, BUS104: 2,54/0,8
C1, C2, C3, C4, C5, C6, C7, C8, C9, C10, C11, C12, C13, C14: C-US075-032X103; C075-032X103
C15, C37, C38, C39, C40: CPOL-USE22-6AXIAL; E22-6
R5, R7: 390; 0207/10
R6, R8: 750; 0207/10
U$2: QUAD; EDGE-CON8

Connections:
!BREAK_CYCLE: BUS43.1, U$2.BL2
!BRK_DATA_CONT: BUS44.1, U$2.BK2
!BRK_IN_PROG: BUS48.1, U$2.BE2
!BUS_STROBE: BUS61.1, U$2.CK1
!C0: BUS65.1, U$2.CE1; also elsewhere on the board
!C1: BUS63.1, U$2.CH1; also elsewhere on the board
!C2: BUS62.1, U$2.CJ1; also elsewhere on the board
!CPMA_DISABLE: BUS53.1, U$2.CU1
!D: U$2.DK2
!DATA0: BUS5.1, BUS19.1, U$2.AR1; also elsewhere on the board
!DATA1: BUS4.1, U$2.AS1; also elsewhere on the board
!DATA2: BUS2.1, U$2.AU1; also elsewhere on the board
!DATA3: BUS1.1, U$2.AV1; also elsewhere on the board
!DATA4: BUS29.1, U$2.BR1; also elsewhere on the board
!DATA5: BUS28.1, U$2.BS1; also elsewhere on the board
!DATA6: BUS26.1, U$2.BU1; also elsewhere on the board
!DATA7: BUS25.1, U$2.BV1; also elsewhere on the board
!DATA8: BUS87.1, U$2.DR1; also elsewhere on the board
!DATA9: BUS86.1, U$2.DS1; also elsewhere on the board
!DATA10: BUS84.1, U$2.DU1; also elsewhere on the board
!DATA11: BUS83.1, U$2.DV1; also elsewhere on the board
!E: U$2.DL2
!EMA0: U$2.AD2
!EMA1: U$2.AE2
!EMA2: U$2.AH2
!F: U$2.DJ2
!FSET: U$2.DP2
!IND1: U$2.CU2
!IND2: U$2.CV2
!INTERNAL_IO: BUS60.1, U$2.CL1; also elsewhere on the board
!INT_RQST: BUS57.1, U$2.CP1; also elsewhere on the board
!IO_PAUSE: BUS66.1, U$2.CD1; also elsewhere on the board
!IR0: U$2.DD2
!IR1: U$2.DE2
!IR2: U$2.DH2
!KEY_CONT: U$2.DU2
!LA_ENABLE: U$2.BM2
!LINK: BUS17.1, U$2.AV2
!LINK_DATA: BUS70.1, U$2.CR2
!LINK_LOAD: BUS69.1, U$2.CS2
!LOAD_CONT: BUS46.1, U$2.BH2
!MA00: BUS15.1, U$2.AD1
!MA01: BUS14.1, U$2.AE1
!MA02: BUS12.1, U$2.AH1
!MA03: BUS11.1, U$2.AJ1
!MA04: BUS39.1, U$2.BD1
!MA05: BUS38.1, U$2.BE1
!MA06: BUS36.1, U$2.BH1
!MA08: BUS101.1, U$2.DD1
!MA09: BUS100.1, U$2.DE1
!MA10: BUS98.1, U$2.DH1
!MA11: BUS93.1, U$2.DJ1
!MD00: BUS10.1, U$2.AK1
!MD01: BUS9.1, U$2.AL1
!MD02: BUS8.1, U$2.AM1
!MD03: BUS6.1, U$2.AP1; also elsewhere on the board
!MD04: BUS34.1, U$2.BK1; also elsewhere on the board
!MD05: BUS33.1, U$2.BL1; also elsewhere on the board
!MD06: BUS32.1, U$2.BM1; also elsewhere on the board
!MD07: BUS30.1, U$2.BP1; also elsewhere on the board
!MD08: BUS92.1, U$2.DK1; also elsewhere on the board
!MD09: BUS91.1, U$2.DL1; also elsewhere on the board
!MD10: BUS90.1, U$2.DM1; also elsewhere on the board
!MD11: BUS88.1, U$2.DP1; also elsewhere on the board
!MD_DIR: BUS21.1, U$2.AK2
!MEM_START: U$2.AJ2
!MS_DISABLE: BUS52.1, U$2.CV1
!NOT_LAST_TR: BUS59.1, U$2.CM1
!NTS_STALL: U$2.BR2
!OVERFLOW: BUS45.1, U$2.BJ2
!ROM_ADDR: U$2.AU2
!RUN: U$2.BU2
!SKIP: BUS55.1, U$2.CS1; also elsewhere on the board
!STOP: U$2.DS2
!TS1: BUS75.1, U$2.CK2
!TS2: BUS74.1, U$2.CL2
!TS3: BUS73.1, U$2.CM2
!TS4: BUS71.1, U$2.CP2
!USER_MODE: U$2.DM2
+15V: BUS104.1, U$2.DA2
-15V: BUS103.1, U$2.AB2, U$2.BB2, U$2.CB2, U$2.DB2
GND: BUS3.1, BUS7.1, BUS13.1, BUS16.1, BUS18.1, BUS20.1, BUS22.1, BUS23.1, BUS27.1, BUS31.1, BUS37.1, BUS40.1, BUS41.1, BUS42.1, BUS47.1, BUS50.1, BUS54.1, BUS58.1, BUS64.1, BUS67.1, BUS68.1, BUS72.1, BUS78.1, BUS81.1, BUS85.1, BUS89.1, BUS94.1, BUS95.1, BUS96.1, BUS97.1, BUS99.1, BUS102.1, C1.2, C2.2, C3.2, C4.2, C5.2, C6.2, C7.2, C8.2, C9.2, C10.2, C11.2, C12.2, C13.2, C14.2, C15.-, C37.-, C38.-, C39.-, C40.-, R6.1, R8.1, U$2.AC1, U$2.AC2, U$2.AF1, U$2.AF2, U$2.AN1, U$2.AN2, U$2.AT1, U$2.AT2, U$2.BC1, U$2.BC2, U$2.BF1, U$2.BF2, U$2.BN1, U$2.BN2, U$2.BT1, U$2.BT2, U$2.CC1, U$2.CC2, U$2.CF1, U$2.CF2, U$2.CN1, U$2.CN2, U$2.CT1, U$2.CT2, U$2.DC1, U$2.DC2, U$2.DF1, U$2.DF2, U$2.DN1, U$2.DN2, U$2.DT1, U$2.DT2; also elsewhere on the board
INHIBIT: U$2.AP2
INITIALIZE: BUS56.1, U$2.CR1; also elsewhere on the board
INT_IN_PROG: U$2.BP2
INT_STROBE: BUS49.1, U$2.BD2
MA07: BUS35.1, U$2.BJ1
unnamed: 3V1.1, R5.1, R6.2
unnamed: 3V2.1, R7.1, R8.2
POWER_OK: U$2.BV2
PULSE_LA: U$2.DR2
RETURN: U$2.AR2
SOURCE: U$2.AL2
STROBE: U$2.AM2
SWITCH: U$2.DV2
TP1: BUS80.1, U$2.CD2
TP2: BUS79.1, U$2.CE2
TP3: BUS77.1, U$2.CH2; also elsewhere on the board
TP4: BUS76.1, U$2.CJ2
VCC: BUS24.1, BUS51.1, BUS82.1, C1.1, C2.1, C3.1, C4.1, C5.1, C6.1, C7.1, C8.1, C9.1, C10.1, C11.1, C12.1, C13.1, C14.1, C15.+, C37.+, C38.+, C39.+, C40.+, R5.2, R7.2, U$2.AA2, U$2.BA2, U$2.CA2; also elsewhere on the board
WRITE: U$2.AS2

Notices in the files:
parts and their libraries:
SparkFun-Hardware: Licensing: Creative Commons ShareAlike 4.0 International - https://creativecommons.org/licenses/by-sa/4.0
